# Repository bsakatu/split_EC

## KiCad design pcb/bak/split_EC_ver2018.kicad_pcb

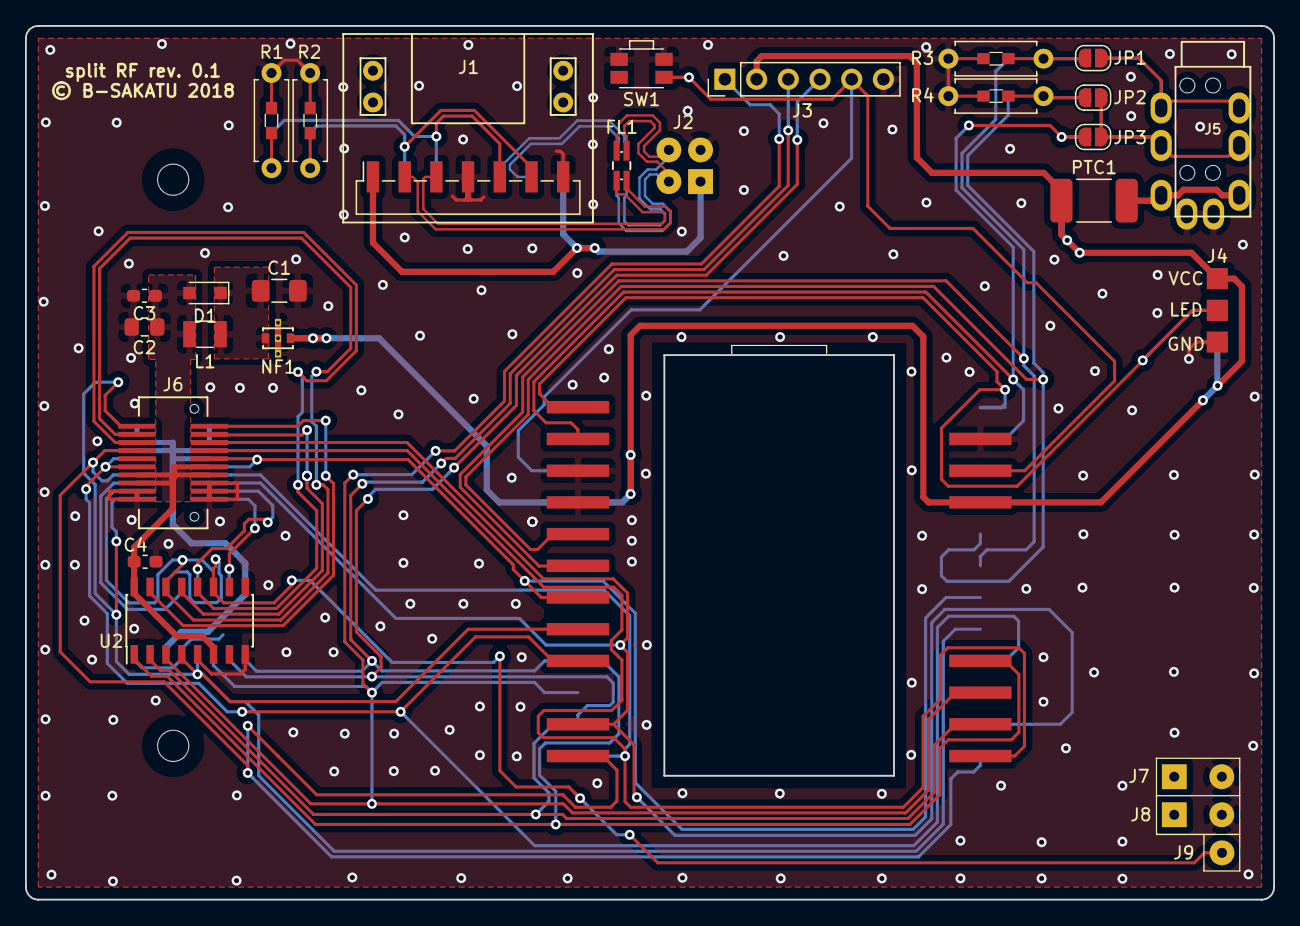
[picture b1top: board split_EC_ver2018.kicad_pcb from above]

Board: 2 copper layers, 100.0 x 70.0 mm, 29 parts (1 on the bottom side), 33 nets.

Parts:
C1: 10u; C_1206_3216Metric_Pad1.42x1.75mm_HandSolder_Reversible
C2: 22u; C_0805_2012Metric_Pad1.15x1.40mm_HandSolder_Reversible
C3: 0.1u; C_0603_1608Metric_Pad1.05x0.95mm_HandSolder_Reversible
C4, C5: 0.1u; C_0603_1608Metric_Pad1.05x0.95mm_HandSolder
D1: 1SS352; D_SOD-323_HandSoldering_Reversible
FL1: ACM2012-900-2P-T002; CMF_TDK_ACM2012_HandSoldering_Reversible
J1: AE-USB2.0-TYPE-C; AE-USB2.0-TYPE-C_Reversible
J2: Conn_01x04_USB; SolderWirePad_2x02_P2.54mm_Drill0.8mm
J3: AVR-ISP-6; PinHeader_1x06_P2.54mm_Vertical
J4: Conn_01x03; Pad_LED-tape_P2.54mm_Reversible
J5: TRRS jack: MJ-4PP-9; MJ-4PP-9
J6: DF15(3.2)-20DP-0.65V(56); DF15(3.2)-20DP-0.65V(56)_BracketLess_Reversible
J7, J8: Conn_01x02; SolderWirePad_1x02_P3.81mm_Drill0.8mm
J9: Conn_01x01; SolderWirePad_1x01_Drill0.8mm
JP1, JP2, JP3: SolderJumper_2_Open; SolderJumper-2_P1.3mm_Open_RoundedPad1.0x1.5mm_Reversible
L1: LBR2518T470K; L_Yuden_LB-2518_HandSolder_Reversible
NF1: YFF21PC1E104MT000N; NF_YFF21_HandSoldering_Reversible_2
PTC1: 0ZCG0050AF2C; PTC_0ZCG_1812_4532_Reversible
R1, R2: 5.1k; R_THT&SMD_0603_1608_Axial_DIN0207_L6.3mm_D2.5mm_P7.62mm_Hor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
R3, R4: 4.7k; R_THT&SMD_0603_1608_Axial_DIN0207_L6.3mm_D2.5mm_P7.62mm_Hor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
SW1: SW_Push; SW_SPST_EVQP7A_Reversible
U1: ProMicro; ProMicro_soldered_with_L-shape-PinHeader_reversible
U2: 74LS138; SOIC-16_3.9x9.9mm_P1.27mm_DoubleSide

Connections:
/CC1: J1.5, R1.2
/CC2: J1.6, R2.2
/D+: FL1.4, J2.3
/D-: FL1.2, J2.2
/FL_D+: FL1.3, J1.3
/FL_D-: FL1.1, J1.2
/VBUS: J1.1, J2.1
AVCC: C2.1, C3.1, C4.1, C5.1, D1.2, J6.12, J6.13, J6.14, J6.15, L1.2, U2.6, U2.16
COL_0: J6.2, U2.15
COL_1: J6.3, U2.14
COL_2: J6.4, U2.13
COL_3: J6.5, U2.12
COL_4: J9.1, U2.11
COL_A: J3.3, U1.16, U2.1
COL_B: J3.4, U1.14, U2.2
COL_C: J3.1, U1.15, U2.3
DATA: JP3.1, U1.2
ENABLE: J6.1, U1.8, U2.4
GND: C1.2, C2.2, C3.2, C4.2, C5.2, J1.4, J1.7, J2.4, J3.6, J4.3, J5.S, J6.16, J6.17, J6.18, J6.19, J6.20, J7.2, J8.2, NF1.2, R1.1, R2.1, R3.2, R4.2, SW1.2, U1.3, U1.4, U1.23, U2.5, U2.8
KEY: J6.10, U1.7
LED: J4.2, U1.1
unnamed: C1.1, D1.1, L1.1, NF1.3
unnamed: J5.R1, JP2.2, JP3.2
unnamed: J5.R2, JP1.2
unnamed: J5.T, PTC1.2
PREV: J6.11, U1.9
ROW_A: J6.6, U1.11
ROW_B: J6.7, U1.12
ROW_C: J6.8, U1.13
SCL: JP1.1, R3.1, U1.6
SDA: JP2.1, R4.1, U1.5
VCC: J3.2, J4.1, NF1.1, PTC1.1, U1.21
~RST: J3.5, SW1.1, U1.22

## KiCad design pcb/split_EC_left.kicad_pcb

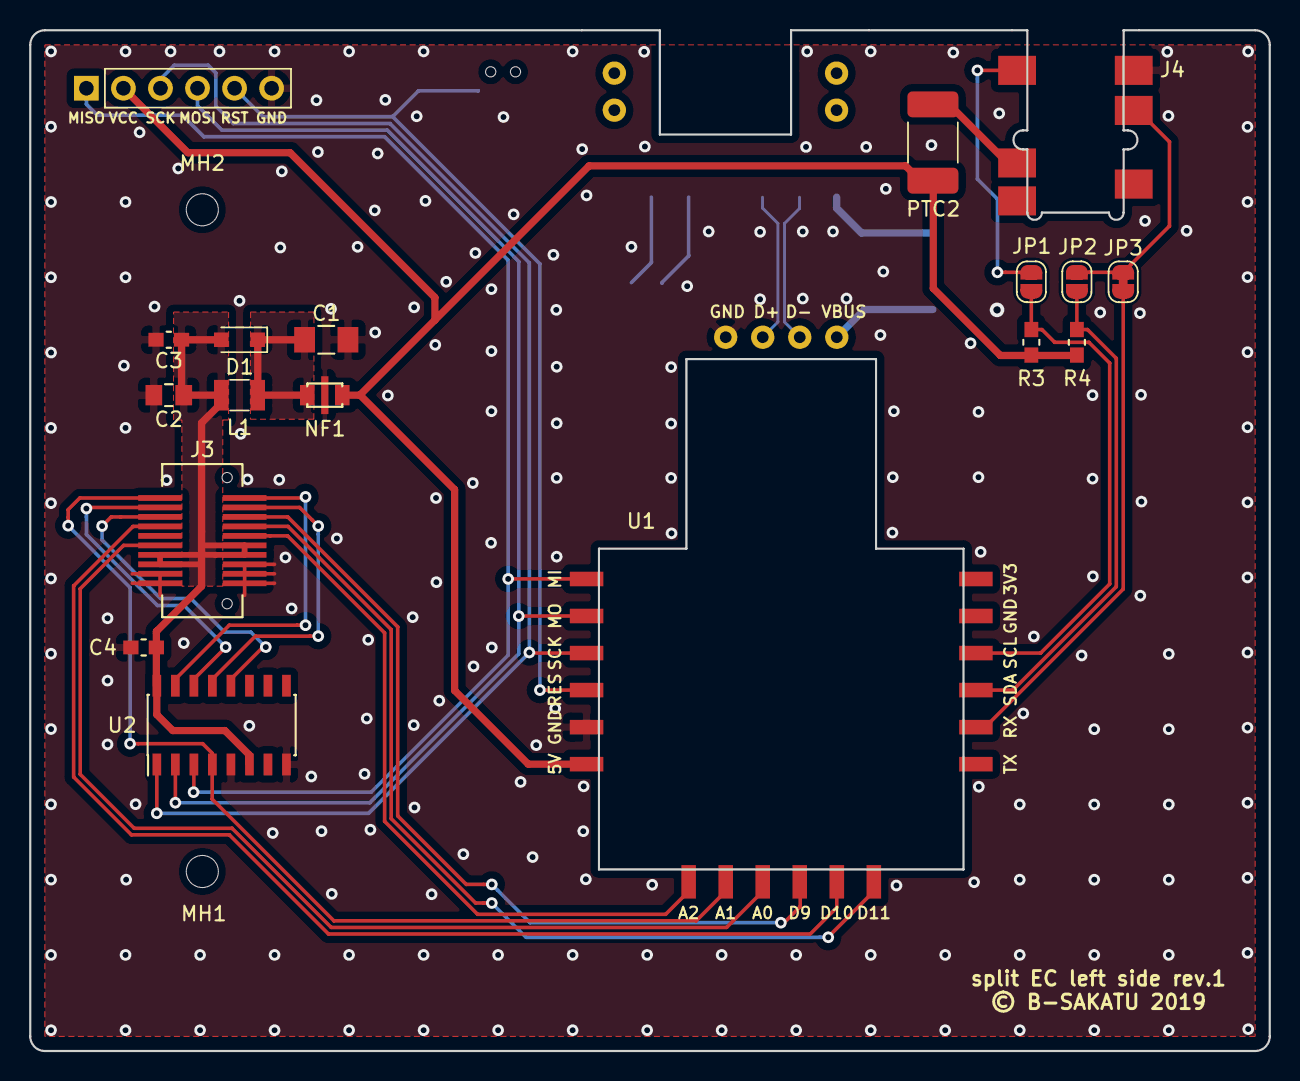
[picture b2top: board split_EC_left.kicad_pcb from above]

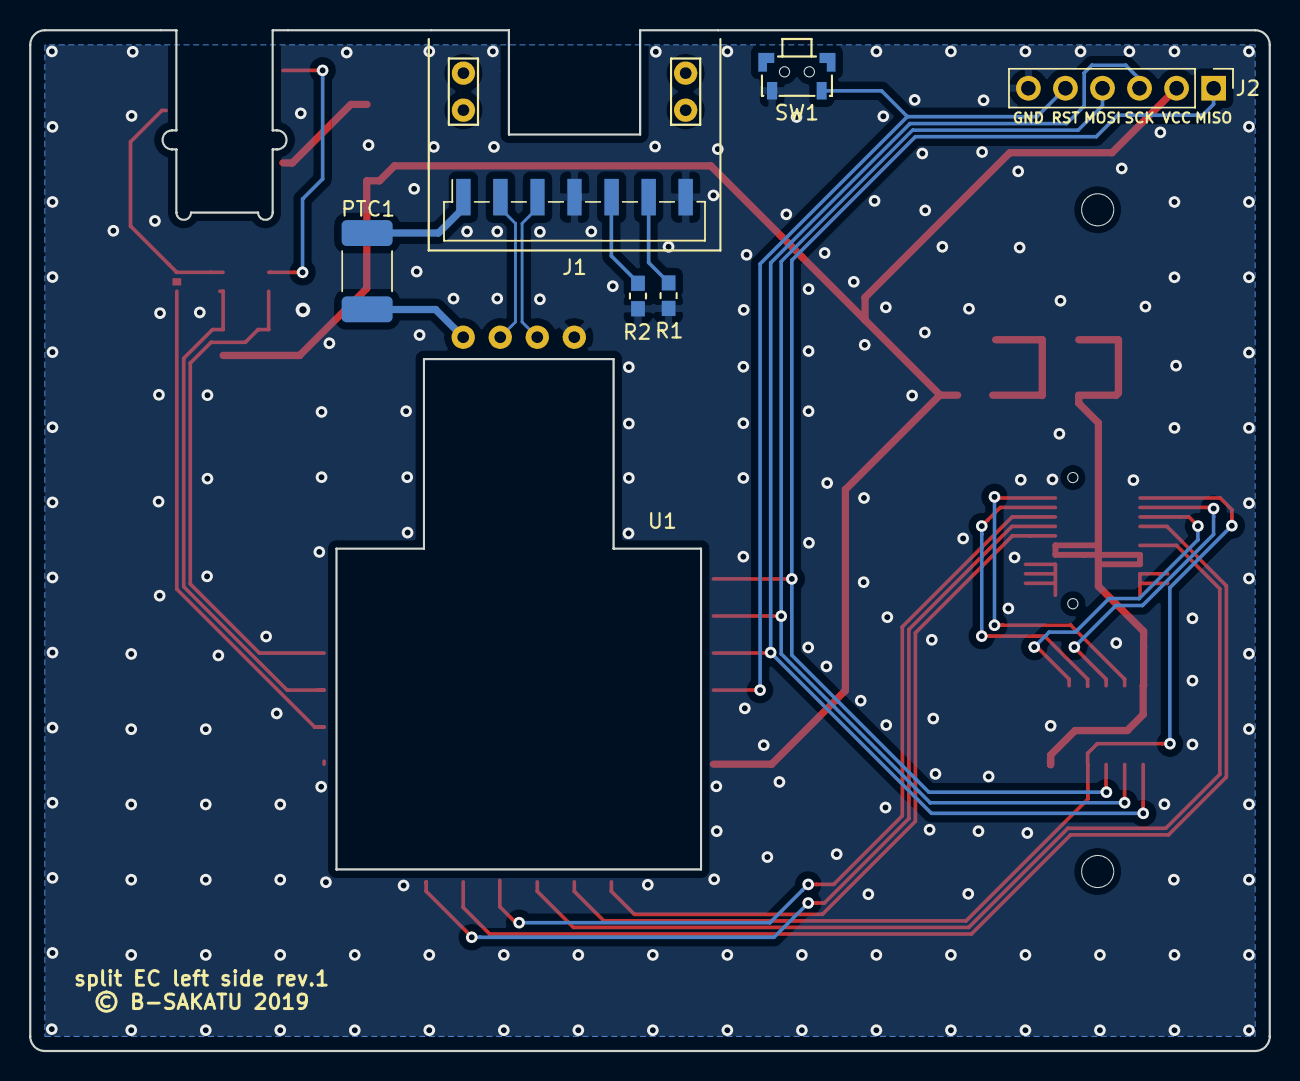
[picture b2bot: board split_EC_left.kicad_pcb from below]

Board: 2 copper layers, 85.0 x 70.0 mm, 25 parts (6 on the bottom side), 30 nets.

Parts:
C1: 10u; C_1206_3216Metric_Pad1.42x1.75mm_HandSolder
C2: 22u; C_0805_2012Metric_Pad1.15x1.40mm_HandSolder
C3, C4: 0.1u; C_0603_1608Metric_Pad1.05x0.95mm_HandSolder
D1: 1SS352; D_SOD-323_HandSoldering
J1: AE-USB2.0-TYPE-C; USB_C_AE-USB2.0-TYPE-C_soldered_with_L-shape-PinHeader
J2: AVR-ISP-6; Connector_AVR-ISP-6_6x1_Reversible
J3: DF15(3.2)-20DP-0.65V(56); DF15(3.2)-20DP-0.65V(56)_BracketLess
J4: TRRS jack; Jack_3.5mm_CUI_SJ-43504-SMT_Horizontal
JP1, JP2: SolderJumper_2_Open; SolderJumper-2_P1.3mm_Open_RoundedPad1.0x1.5mm
JP3: SolderJumper_2_Open; SolderJumper-2_P1.3mm_Bridged_RoundedPad1.0x1.5mm
L1: LBR2518T470K; L_Yuden_LB-2518_HandSolder
MH1, MH2: MountingHole; MountingHole_2.2mm_M2
NF1: YFF21PC1E104MT000N; NF_YFF21_HandSoldering
PTC1, PTC2: 0ZCG0050AF2C; PTC_0ZCG_1812_4532
R1, R2: 5.1k; R_SMD_0603_1608_HandSolder
R3, R4: 4.7k; R_SMD_0603_1608_HandSolder
SW1: SW_Push; SW_SPST_4.4x1.8x3.8mm_plastic-pin
U1: BeetleUSB_with_USB; Module_BeetleUSB_soldered_with_L-shape-PinHeader_Reverse
U2: 74LS138; SOIC-16_3.9x9.9mm_P1.27mm

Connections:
/CC1: J1.5, R2.2
/CC2: J1.6, R1.2
/D+: J1.3, U1.20
/D-: J1.2, U1.21
AVCC: C2.1, C3.1, C4.1, D1.2, J3.12, J3.13, J3.14, J3.15, L1.2, U2.6, U2.16
COL_0: J3.2, U2.15
COL_1: J3.3, U2.14
COL_2: J3.4, U2.13
COL_3: J3.5, U2.12
COL_A: J2.3, U1.16, U2.1
COL_B: J2.4, U1.17, U2.2
COL_C: J2.1, U1.18, U2.3
DATA: JP3.1, U1.5
ENABLE: J3.1, U1.11, U2.4
GND: C1.2, C2.2, C3.2, C4.2, J1.4, J1.7, J2.6, J3.16, J3.17, J3.18, J3.19, J3.20, J4.S, NF1.2, R1.1, R2.1, SW1.2, U1.14, U1.19, U2.5, U2.8
KEY: J3.10, U1.12
unnamed: C1.1, D1.1, L1.1, NF1.3
unnamed: J4.R1, JP2.2, JP3.2
unnamed: J4.R2, JP1.2
unnamed: J4.T, PTC2.2
unnamed: PTC1.2, U1.22
PREV: J3.11, U1.10
ROW_A: J3.6, U1.9
ROW_B: J3.7, U1.8
ROW_C: J3.8, U1.7
SCL: JP1.1, R3.2, U1.3
SDA: JP2.1, R4.2, U1.4
VBUS: J1.1, PTC1.1
VCC: J2.2, NF1.1, PTC2.1, R3.1, R4.1, U1.13
~RST: J2.5, SW1.1, U1.15

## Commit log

2018-09-17 add PCB datas at first time.
2018-09-17 add schematic pdf folder and pdf file as of 2018/09/18
2018-09-25 update schematic file.
2018-09-25 add kicad library and parts as submodule.
2019-05-02 Update and rename pcb design datas
2019-05-02 Update symbols and footprints
2019-05-02 Add old pcb design files
2019-05-02 Add pcb design files for right side
2019-05-02 Add latest schematic pdf file and Rename old one
2019-05-12 Add and Delete schematic pdf
    - Add latest and first release version of schematic pdf.
    - Delete previous schematic pdf because I2C registers are pull-downed.
    Its should be pull-uped.
2019-05-12 Add gerber datas of rev.1
2019-05-12 Update to latest
2019-05-19 Update footprint library to latest

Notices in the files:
pcb/bak/split_EC_ver2018.kicad_pcb:
© B-SAKATU 2018
pcb/split_EC_left.kicad_pcb:
© B-SAKATU 2019
